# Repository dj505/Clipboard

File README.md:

# Clipboard
A macropad made to make copy/paste easier  

## Isn't this basically just a small macropad?
Yes! There's no reason you have to use this exclusively for copy/pasting, or other common shortcuts. You can do whatever you want with it, really. I was comissioned to design this by a friend who does a lot of copy/pasting at work. As he would like to save himself from a perpetually sore wrist, it was designed to the specifications he provided, right down to the specific intended use case. Since it's meant to be used for copying and pasting in an office-like environment, "Clipboard" just so happened to be a good play on words. (Shoutouts to clue for pointing that out!)

## RP2040-Zero Branch
The RP2040 Zero is significantly cheaper than the Tiny2040 and has more IO. Those extra pins aren't connected on the PCB itself, but you can solder wires to them easily enough if you want to add extra peripherals to the Clipboard. The firmware should also work without any changes as the pinout is nearly identical!

# Bill of Materials

|       Part       |      Package      | Qty |
|------------------|-------------------|-----|
| 100nF Capacitor  | 0805              | 3   |
| 1N4148 Diode     | DO-35             | 4   |
| SK6812MINI-E     | MINI-E            | 3   |
| Keyboard Switch  | MX-style          | 3   |
| Rotary Encoder   | PEC12R-4215F-S0024| 1   |
| RP2040-Zero      | N/A               | 1   |
| SN74LV1T34DBV    | SOT-23-5          | 1   |

# Firmware
This board was developed using [KMK Firmware](https://github.com/KMKfw/kmk_firmware). Instructions for setting up KMK on your board can be found in the [Getting Started](https://github.com/KMKfw/kmk_firmware/blob/master/docs/en/Getting_Started.md) docs.

After KMK itself is set up, delete the existing `code.py` or `main.py` on the CIRCUITPY drive, and copy the `code.py` file in this repository's "keymap" directory to the root of the drive.

You're done!

## Notes on the firmware
- By default, it does a lot. Maybe too much. *Probably* too much, actually. Please feel free to edit it down for your own use case! The [KMK docs](http://kmkfw.io/docs/) are your friend.
- The OLED code used here is currently undocumented. It's fully reworked from example code I found on a GitHub issue thread that I can't seem to find again. It should be straightforward enough to understand, though!

## Required CircuitPython libraries
CircuitPython libraries can be found [here.](https://circuitpython.org/libraries)  
This project will require the following libraries from the "lib" folder of the library bundle:
* neopixel.mpy
* adafruit_displayio_ssd1306.mpy (required for OLED)
* adafruit_display_text (required for OLED)  
Copy these files and folders into the "lib" folder on your CIRCUITPY drive.

## Connecting an OLED display
Clipboard is made with an I2C 128x64 SSD1306 OLED display in mind. If you have a different display with a different resolution, you will have to edit `code.py` accordingly. The underside of the board has the appropriate pins marked, with **SDA on GP26** and **SCL on GP27**. The VCC (or VDD (or 3.3V)) pin on the OLED should be wired to the +3V3 pin on the Clipboard.

# Credits
* [Tiny2040 Symbol & Footprint](https://github.com/chinatsu/tiny2040) by [chinatsu](https://github.com/chinatsu) - Licensed under Creative Commons Attribution-ShareAlike 3.0 Unported. License can be found in `rp2040` directory. The following changes were made to the pcbnew footprint for this project:
    * "U1" and "Tiny2040" text on silkscreen layer have been moved
    * Rectangular pads were added to the front copper layer to allow for surface mounting
    * Silkscreen outline was changed so as to not overlap with the rectangular pads
* [marbastlib](https://github.com/ebastler/marbastlib) by [ebastler](https://github.com/ebastler) - Licensed under the CERN Open Hardware Licence Version 2 - Permissive.
* [MX_V2](https://github.com/ai03-2725/MX_V2) and [MX_Alps_Hybrid](https://github.com/ai03-2725/MX_Alps_Hybrid) by [ai03](https://github.com/ai03-2725) - Both licensed under the MIT License.

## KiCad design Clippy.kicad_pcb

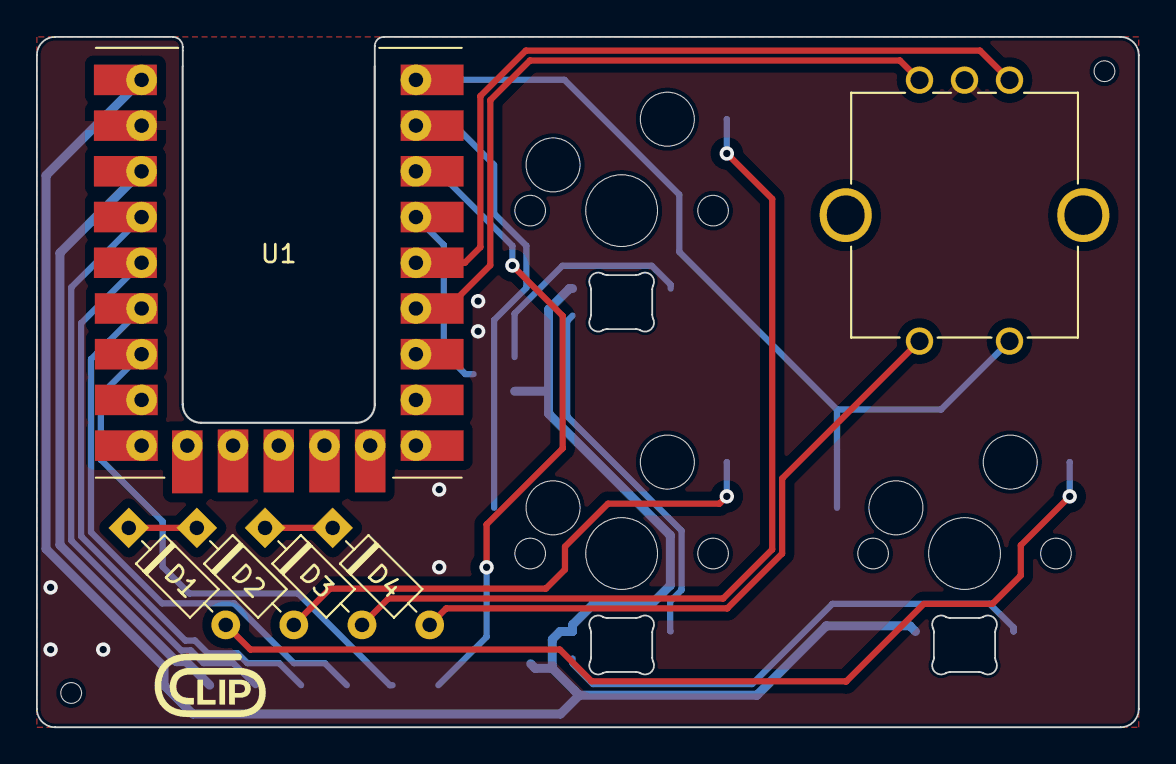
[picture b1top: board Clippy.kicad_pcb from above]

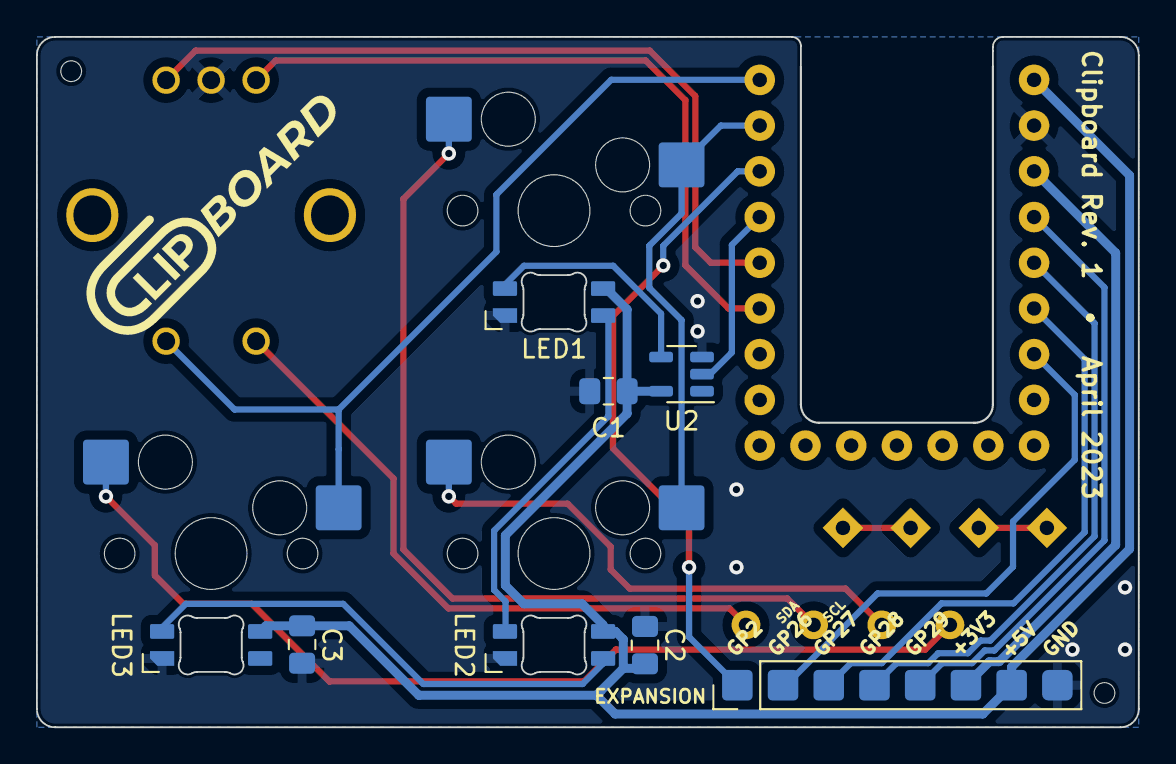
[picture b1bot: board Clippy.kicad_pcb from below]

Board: 2 copper layers, 61.2 x 38.3 mm, 17 parts (8 on the bottom side), 22 nets.

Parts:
C1, C2, C3: 100nF; C_0805_2012Metric_Pad1.18x1.45mm_HandSolder
D1, D2, D3, D4: 1N4148; D_DO-35_SOD27_P7.62mm_Horizontal
J1: Conn_01x08; PinHeader_1x08_P2.54mm_Vertical
LED1, LED2, LED3: SK6812MINI-E; LED_MX_6028R
MX1, MX2, MX3: MX-NoLED; MX-Hotswap-1U
SW1: PEC12R-4215F-S0024; RotaryEncoder_Bourns_Vertical_PEC12R-3xxxF-Sxxxx
U1: RP2040-Zero; RP2040 Zero
U2: SN74LV1T34DBV; SOT-23-5

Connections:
+3.3V: J1.6, U1.3 (3V3)
+5V: C1.2, C2.1, C3.1, J1.7, LED1.1 (VDD), LED2.1 (VDD), LED3.1 (VDD), U1.1 (5V), U2.5 (VCC)
COL0: MX1.1 (COL), MX2.1 (COL), U1.11 (GP1)
COL1: MX3.1 (COL), SW1.S1, U1.10 (GP0)
ENCA: SW1.A, U1.14 (GP4)
ENCB: SW1.B, U1.15 (GP5)
GND: C1.1, C2.2, C3.2, J1.8, LED1.4 (VSS), LED2.4 (VSS), LED3.4 (VSS), SW1.C, U1.2 (GND), U2.3 (GND)
GP2: J1.1, U1.12 (GP2)
GP26: J1.2, U1.7 (GP26)
GP27: J1.3, U1.6 (GP27)
GP28: J1.4, U1.5 (GP28)
GP29: J1.5, U1.4 (GP29)
LED_DIN: LED1.3 (DIN), U2.4 (Y)
LED_SIGNAL: U1.13 (GP3), U2.2 (A)
unnamed: D1.2 (A), MX3.2 (ROW)
unnamed: D2.2 (A), MX2.2 (ROW)
unnamed: D3.2 (A), MX1.2 (ROW)
unnamed: D4.2 (A), SW1.S2
unnamed: LED1.2 (DOUT), LED2.3 (DIN)
unnamed: LED2.2 (DOUT), LED3.3 (DIN)
ROW0: D3.1 (K), D4.1 (K)
ROW1: D1.1 (K), D2.1 (K)

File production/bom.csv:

Designator,Footprint,Quantity,Value,LCSC Part #
"C1, C2, C3",0805,3,100nF,C1525
"D1, D2, D3, D4",D_DO-35_SOD27_P7.62mm_Horizontal,4,1N4148,
J1,PinHeader_1x08_P2.54mm_Vertical,1,Conn_01x08,
"LED1, LED2, LED3",LED_MX_6028R,3,SK6812MINI-E,
"MX1, MX2, MX3",MX-Hotswap-1U,3,MX-NoLED,
SW1,RotaryEncoder_Bourns_Vertical_PEC12R-3xxxF-Sxxxx,1,PEC12R-4215F-S0024,
U1,RP2040 Zero,1,RP2040-Zero,
U2,SOT-23-5,1,SN74LV1T34DBV,C100024

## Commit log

2023-04-25 Final touches?
2023-04-25 Add tooling holes
2023-04-25 oops. Actually add tooling holes
2023-04-25 Fix DRC errors to a reasonable extent
2023-04-25 finishing touches
2023-04-26 finishing touches 2 electric boogaloo
2023-04-27 oops rows were swapped in the schematic
2023-04-28 Edit schematic labels, initial keymap
2023-04-28 keymap changes
2023-05-02 fully working firmware!
2023-05-02 Update keymap
2023-05-03 Version 1.0 release commit
2023-05-03 oops
2023-05-03 oops 2
2023-05-03 redundant example code. lol
2023-05-04 More firmware things, update readme
2023-05-05 RP2040-Zero compatibility
2023-05-05 Fix pad misalignment on RP2040-Zero footprint
2023-05-06 minor change to readme
